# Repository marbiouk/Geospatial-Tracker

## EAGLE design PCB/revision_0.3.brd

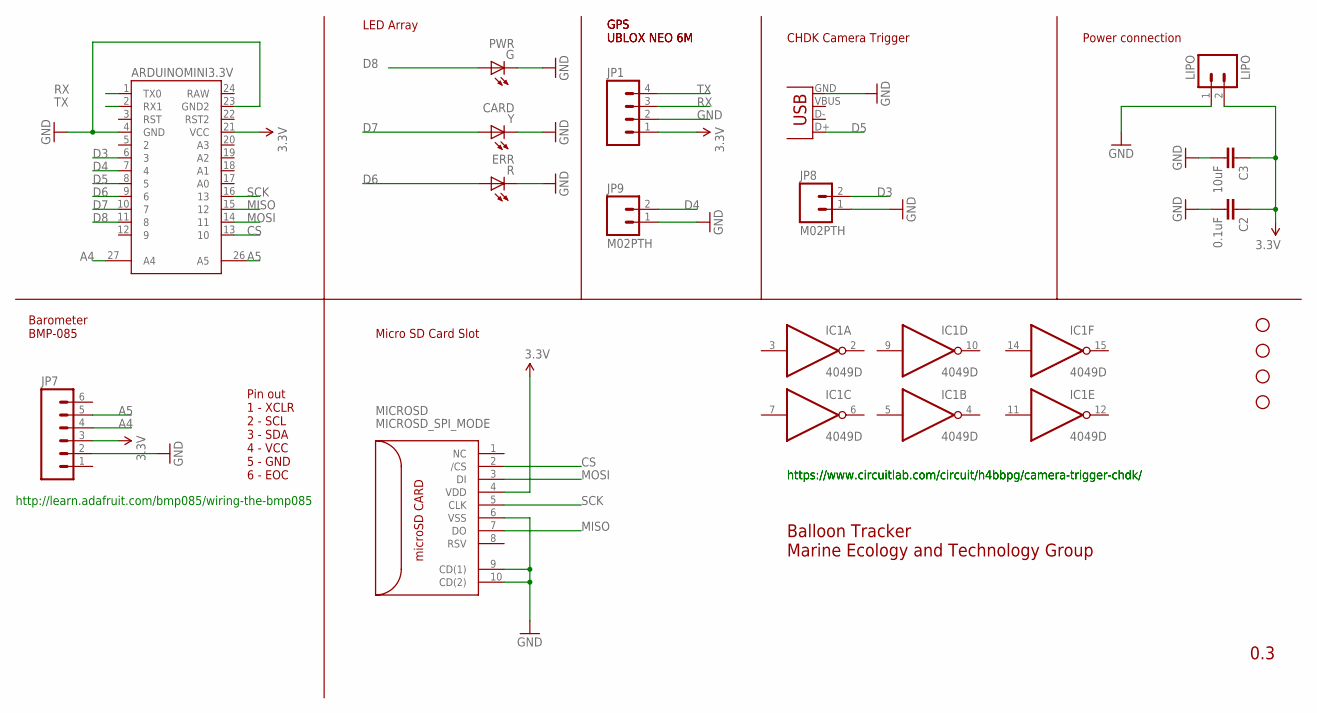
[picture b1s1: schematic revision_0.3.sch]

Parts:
ARDUINOMINI3.3V: ARDUINO_MINI
C2: 0.1uF; 0805
C3: 10uF; 0805
G: PWR; CHIP-LED0805
IC1: 4049D; SO16
JP1: M04PTH; 1X04
JP2: USB-A-SMD; USB-A-S-NOSILK-FEMALE
JP3, JP4, JP5, JP6: STAND-OFF
JP7: M06SIP; 1X06
JP8, JP9: M02PTH; 1X02
LIPO: LIPO; JST-2-PTH
MICROSD: MICROSD_SPI_MODE; MICRO_SD_CONNECTOR
R: ERR; CHIP-LED0805
Y: CARD; CHIP-LED0805

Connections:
1.0V: JP1.1, JP7.3
3.3V: ARDUINOMINI3.3V.21 (VCC), C2.1, C3.1, LIPO.2, MICROSD.4 (VDD)
A4: ARDUINOMINI3.3V.27 (A4), JP7.4
A5: ARDUINOMINI3.3V.26 (A5), JP7.5
CS: ARDUINOMINI3.3V.13 (10), MICROSD.2 (/CS)
D3: ARDUINOMINI3.3V.6 (3), JP8.2
D4: ARDUINOMINI3.3V.7 (4), JP9.2
D5: ARDUINOMINI3.3V.8 (5), JP2.D+
D6: ARDUINOMINI3.3V.9 (6), R.A
D7: ARDUINOMINI3.3V.10 (7), Y.A
D8: ARDUINOMINI3.3V.11 (8), G.A
GND: ARDUINOMINI3.3V.4 (GND), ARDUINOMINI3.3V.23 (GND2), C2.2, C3.2, G.C, JP1.2, JP2.GND, JP7.2, JP8.1, JP9.1, LIPO.1, MICROSD.6 (VSS), MICROSD.9 (CD(1)), MICROSD.10 (CD(2)), R.C, Y.C
MISO: ARDUINOMINI3.3V.15 (12), MICROSD.7 (DO)
MOSI: ARDUINOMINI3.3V.14 (11), MICROSD.3 (DI)
RX: ARDUINOMINI3.3V.1 (TX0), JP1.3
SCK: ARDUINOMINI3.3V.16 (13), MICROSD.5 (CLK)
TX: ARDUINOMINI3.3V.2 (RX1), JP1.4
VDD: IC1.1 (VDD)
VSS: IC1.8 (VSS)

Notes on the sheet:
LED Array
Power connection
Barometer BMP-085
Micro SD Card Slot
Pin out 1 - XCLR 2 - SCL 3 - SDA 4 - VCC 5 - GND 6 - EOC
Balloon Tracker Marine Ecology and Technology Group
0.3
GPS UBLOX NEO 6M
CHDK Camera Trigger
http://learn.adafruit.com/bmp085/wiring-the-bmp085
https://www.circuitlab.com/circuit/h4bbpg/camera-trigger-chdk/

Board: 2 copper layers, 18 parts (0 on the bottom side), 17 nets, no tracks yet.

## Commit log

2014-02-13 Uploaded PCB files
2014-02-13 RM gitignore

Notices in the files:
parts and their libraries:
SparkFun-Connectors: Licensing: CC v3.0 Share-Alike You are welcome to use this library for commercial purposes.
